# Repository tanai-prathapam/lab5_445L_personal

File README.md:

# Lab 5 Music Player and Audio Amp

# ECE445L-Lab5

Lab 5 Template.

## HW

The hw folder should contain your schematic and board files for your PCB or
circuits. In labs 3-11, you will be creating schematics for your circuit
in Kicad. 

## SW

The sw folder should contain your application firmware and software written for
the lab. The sw/inc folder contains firmware drivers written for you by
Professor Valvano. Feel free to write your own (in fact, in some labs, you may
be required to write your own).

You can place any other source files in the sw/ folder. TAs will look at the
files you create and/or modify for software quality and for running your
project.

## Resources

A couple files are provided in the Resources folder so you don't have to keep
searching for that one TI document. Some of them are immediately useful, like
the TM4C datasheet. Others may be useful for your final project, like the
TM4C_System_Design_Guidelines page.

## Git and Github

We will extensively use Git and Github for managing lab projects. This makes it
easier for TAs to grade and help debug the project by allowing the students to
see commit histories, maintain a common project structure, collaborate with
partners, merge different codebases, and to debug work.

Two common ways of using Git and Github are [Github Desktop](https://desktop.github.com/) and the [command line](https://git-scm.com/downloads). [Tutorials](https://dev.to/mollynem/git-github--workflow-fundamentals-5496) are also abundant on the net for you to peruse. We've provided a cheatsheet for git in the Resources folder.

It is highly recommended to make the most out of Git, even if you've never used
it before. Version control will save you a lot of suffering, and tools like Git
or SVN are ubiquitous in the industry.

## Lab Report

Following the lab doc provided at the root of this project, the TAs request you
submit a lab report in Microsoft Word (or Pages, if you're a Mac user). Please
name it `EID_lab_LAB_NUMBER_report.pdf`.

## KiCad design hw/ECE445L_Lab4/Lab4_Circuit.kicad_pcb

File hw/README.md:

# What to use?

For 319K/445L Lab 6 or 7, use the marked file. Otherwise use ECE445L_Starter.

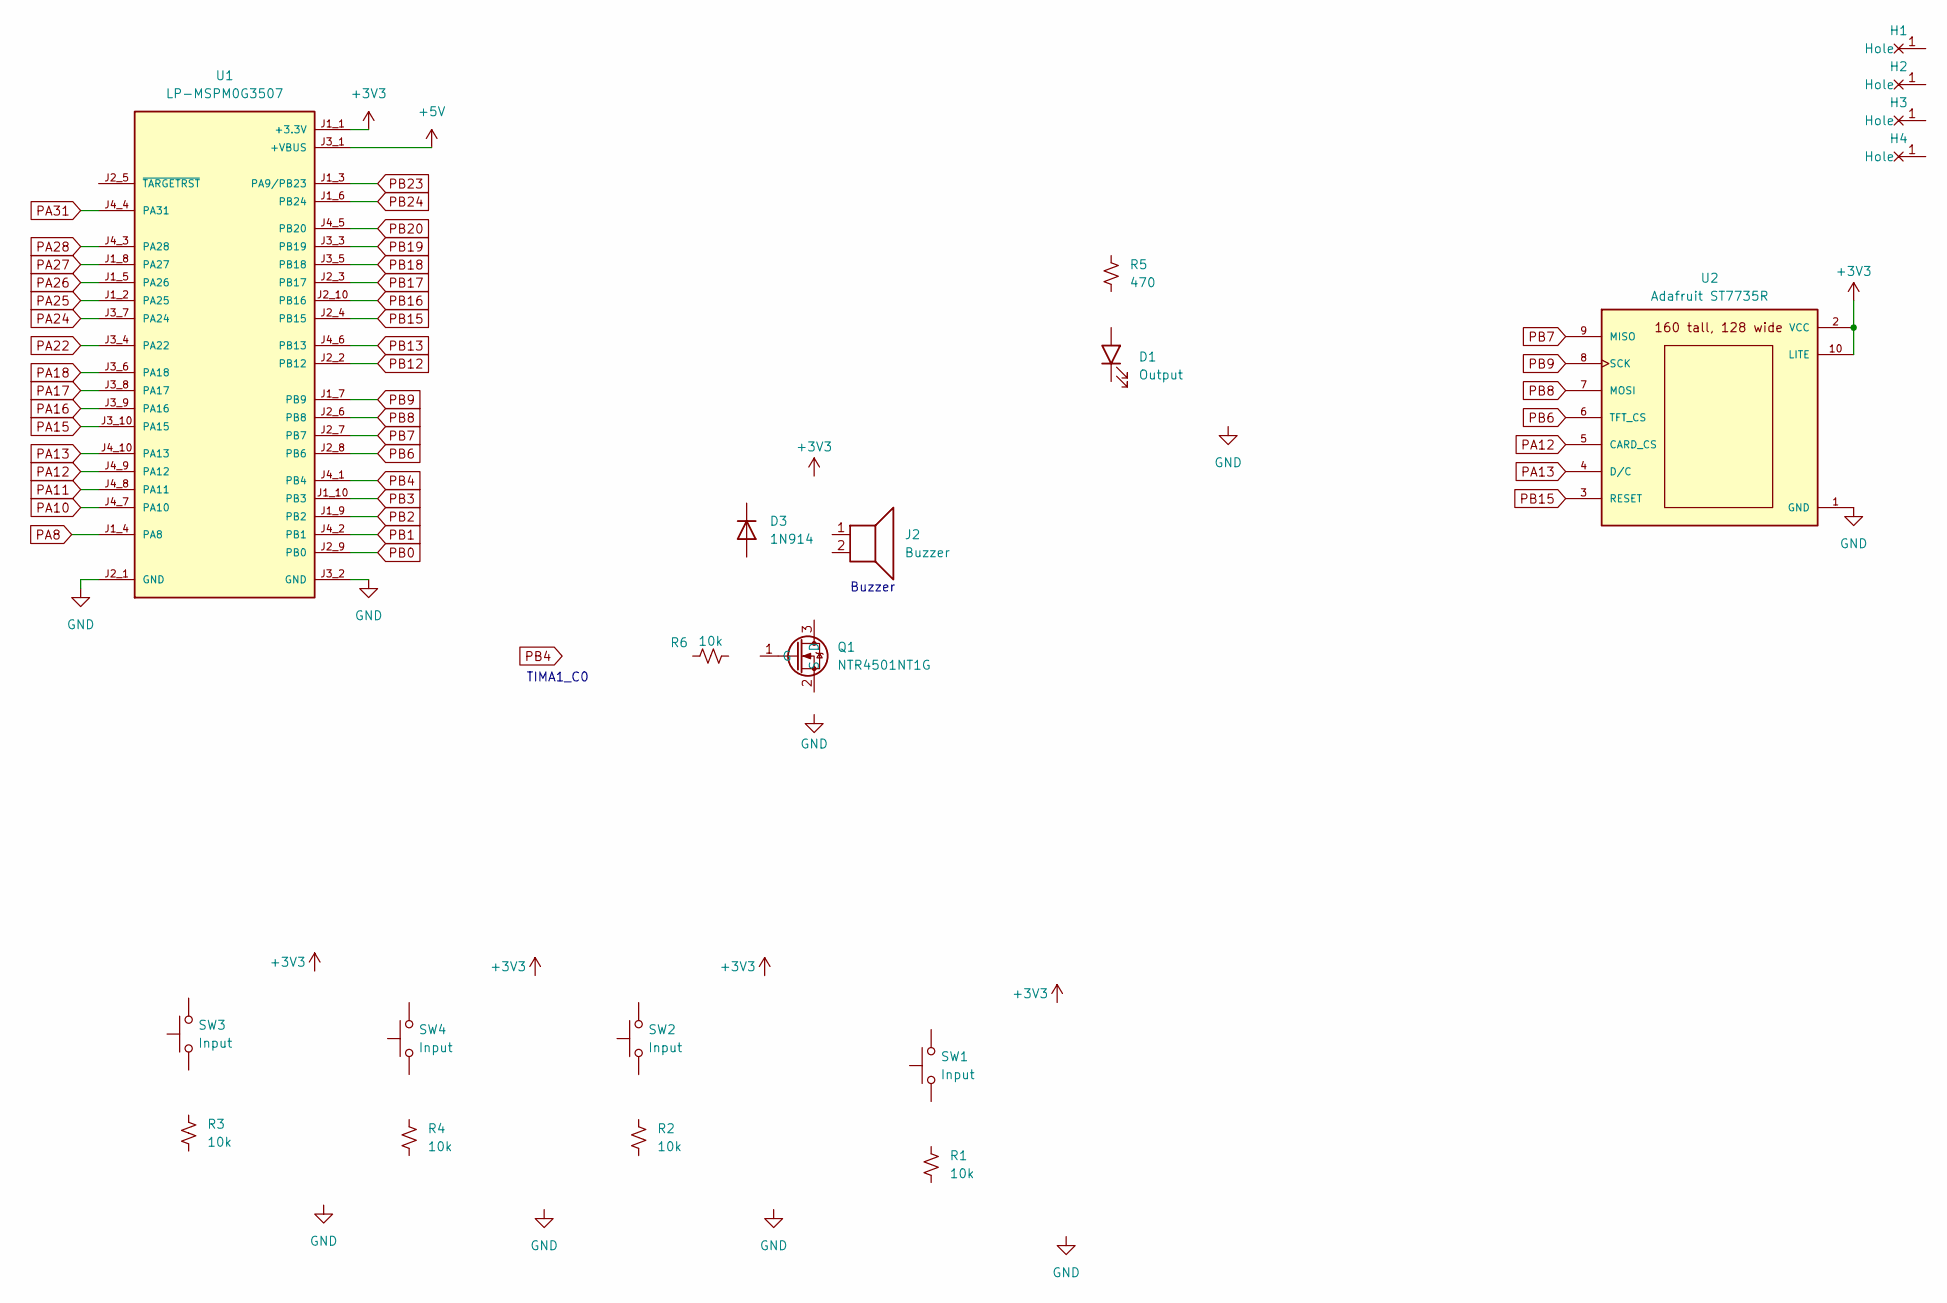
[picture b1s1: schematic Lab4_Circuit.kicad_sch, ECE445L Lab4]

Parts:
D1: Output; LED_D5.0mm
D3: 1N914; D_DO-35_SOD27_P7.62mm_Horizontal
H1, H2, H3, H4: MountingHole_4_40
J2: Buzzer; PinHeader_1x02_P2.54mm_Vertical
Q1: NTR4501NT1G; SOT96P237X111-3N; Mouser Part Number 863-NTR4501NT1G
R1, R2, R3, R4, R6: 10k; R_Axial_DIN0204_L3.6mm_D1.6mm_P7.62mm_Horizontal
R5: 470; R_Axial_DIN0204_L3.6mm_D1.6mm_P7.62mm_Horizontal
SW1, SW2, SW3, SW4: Input; SW_PUSH_6mm
U1: LP-MSPM0G3507; ti_LP_MSPM0G3507
U2: Adafruit ST7735R; adafruit_st7735r2

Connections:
+3V3: U1.J1_1 (+3.3V), U2.2 (VCC), U2.10 (LITE)
+5V: U1.J3_1 (+VBUS)
GND: U1.J2_1 (GND), U1.J3_2 (GND), U2.1 (GND)
PA8: U1.J1_4 (PA8)
PA10: U1.J4_7 (PA10)
PA11: U1.J4_8 (PA11)
PA12: U1.J4_9 (PA12), U2.5 (CARD_CS)
PA13: U1.J4_10 (PA13), U2.4 (D/C)
PA15: U1.J3_10 (PA15)
PA16: U1.J3_9 (PA16)
PA17: U1.J3_8 (PA17)
PA18: U1.J3_6 (PA18)
PA22: U1.J3_4 (PA22)
PA24: U1.J3_7 (PA24)
PA25: U1.J1_2 (PA25)
PA26: U1.J1_5 (PA26)
PA27: U1.J1_8 (PA27)
PA28: U1.J4_3 (PA28)
PA31: U1.J4_4 (PA31)
PB0: U1.J2_9 (PB0)
PB1: U1.J4_2 (PB1)
PB2: U1.J1_9 (PB2)
PB3: U1.J1_10 (PB3)
PB4: U1.J4_1 (PB4)
PB6: U1.J2_8 (PB6), U2.6 (TFT_CS)
PB7: U1.J2_7 (PB7), U2.9 (MISO)
PB8: U1.J2_6 (PB8), U2.7 (MOSI)
PB9: U1.J1_7 (PB9), U2.8 (SCK)
PB12: U1.J2_2 (PB12)
PB13: U1.J4_6 (PB13)
PB15: U1.J2_4 (PB15), U2.3 (RESET)
PB16: U1.J2_10 (PB16)
PB17: U1.J2_3 (PB17)
PB18: U1.J3_5 (PB18)
PB19: U1.J3_3 (PB19)
PB20: U1.J4_5 (PB20)
PB23: U1.J1_3 (PA9/PB23)
PB24: U1.J1_6 (PB24)

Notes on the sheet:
Buzzer
TIMA1_C0

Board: 2 copper layers, 20 parts (1 on the bottom side), 9 nets, no tracks yet.

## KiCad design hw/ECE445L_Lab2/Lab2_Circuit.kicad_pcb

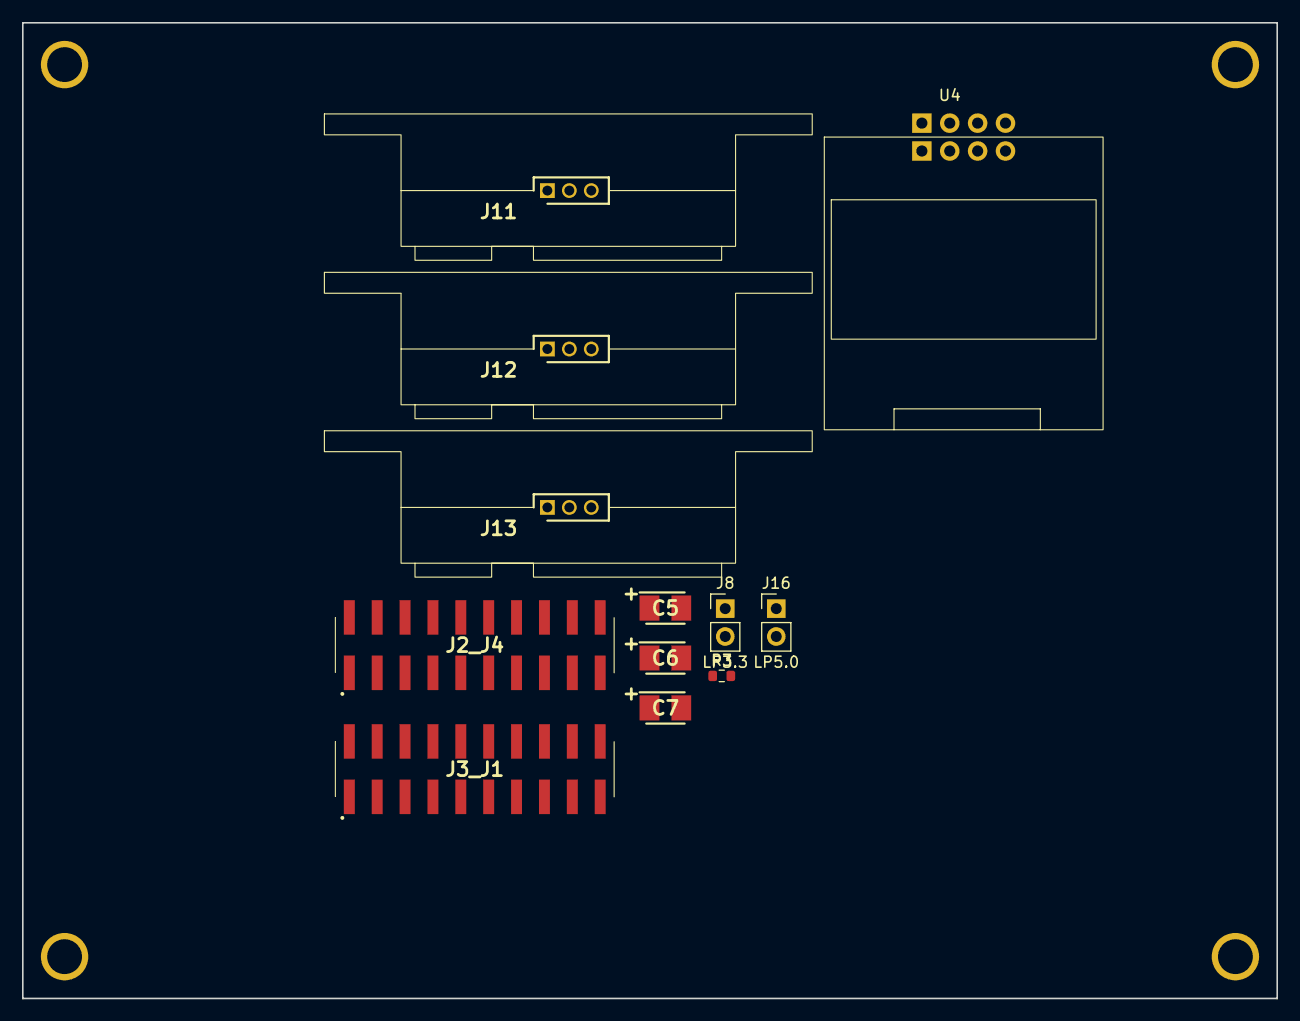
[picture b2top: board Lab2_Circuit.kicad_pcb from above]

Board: 2 copper layers, 114.3 x 88.9 mm, 16 parts (0 on the bottom side), 10 nets, no tracks yet.

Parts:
C5, C6, C7: 10uF; CAPPM3528X210N
H1, H2, H3, H4: MountingHole_4_40
J2_J4, J3_J1: LaunchPad
J8: LP3.3; PinHeader_1x02_P2.54mm_Vertical
J11, J12, J13: GP2Y0A41SK0F; SHDR3W50P0X200_1X3_650X240X440P
J16: LP5.0; PinHeader_1x02_P2.54mm_Vertical
R3: 1.5k; R_0603_1608Metric
U4: SSD1306

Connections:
+3V3: J8.1 (A), R3.1, U4.2 (VCC), U4.5 (VCC)
+5V: C5.1 (+), C6.1 (+), C7.1 (+), J11.3, J12.3, J13.3, J16.2 (B)
/LP3_3: J3_J1.1, J8.2 (B)
/VBUS: J3_J1.2, J16.1 (A)
GND: C5.2 (-), C6.2 (-), C7.2 (-), J2_J4.2, J3_J1.4, J11.2, J12.2, J13.2, U4.1 (GND), U4.6 (GND)
PA24: J3_J1.14, J13.1
PA26: J3_J1.9, J11.1
PB2: J3_J1.17, R3.2, U4.3 (SCL), U4.7 (SCL)
PB3: J3_J1.19, U4.4 (SDA), U4.8 (SDA)
PB24: J3_J1.11, J12.1

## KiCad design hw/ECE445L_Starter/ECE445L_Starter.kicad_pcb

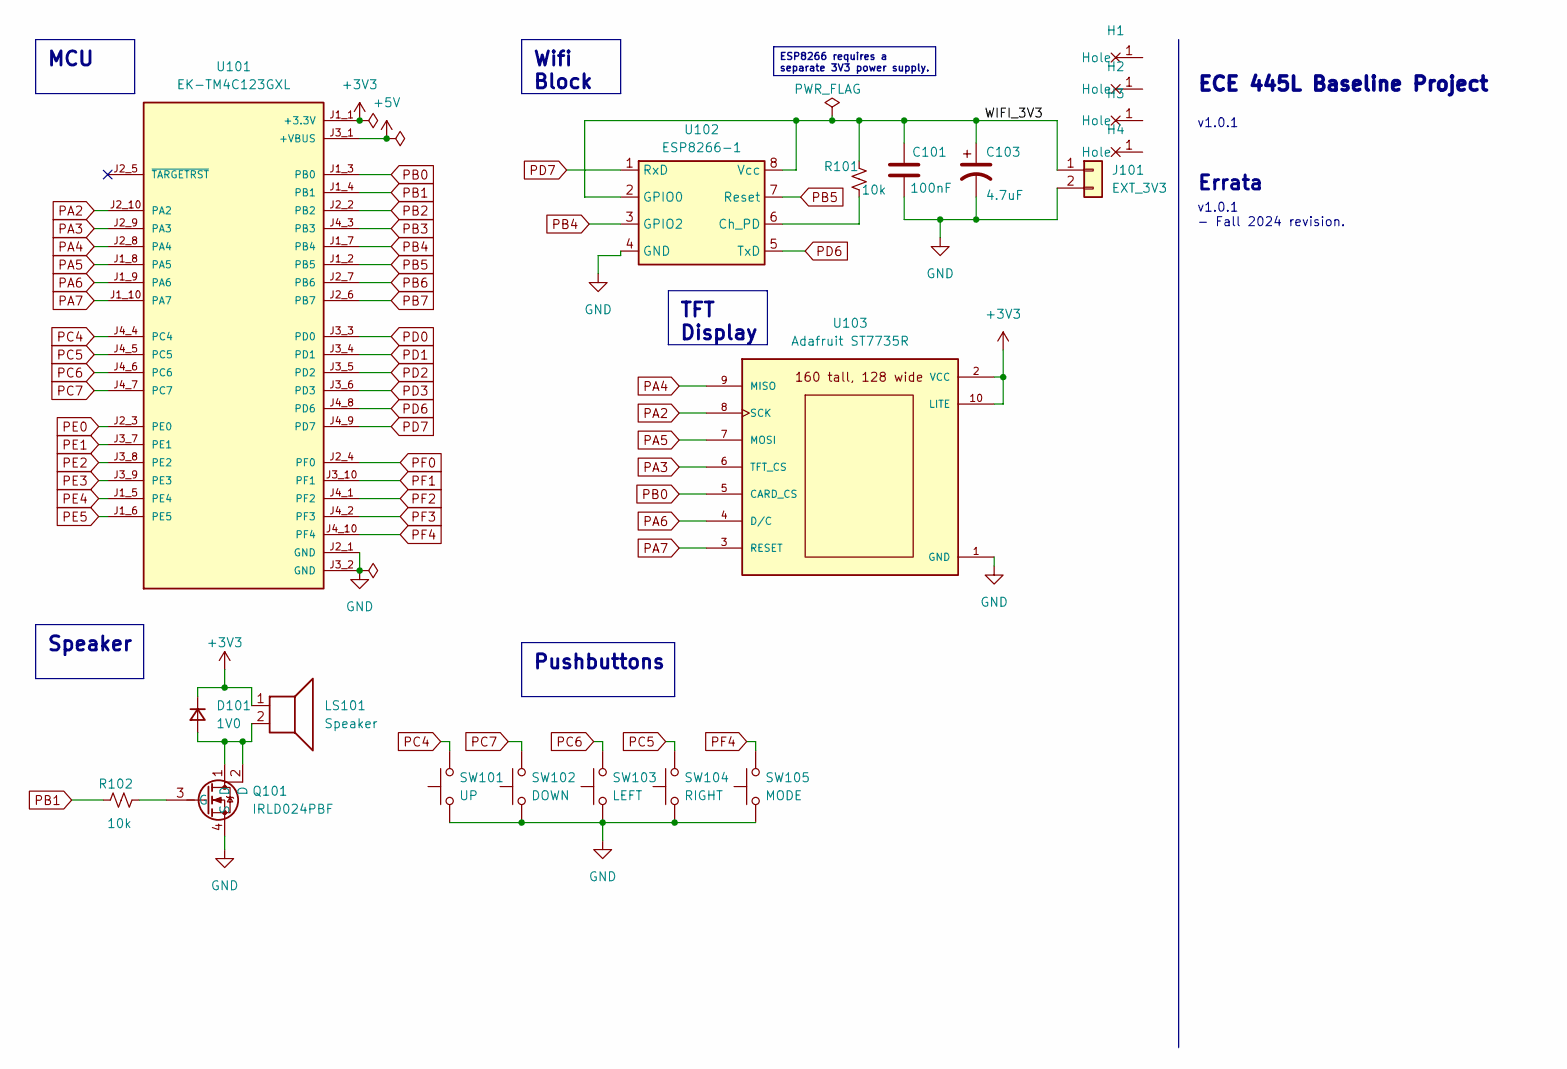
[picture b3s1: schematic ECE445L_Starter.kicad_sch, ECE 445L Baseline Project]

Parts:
C101: 100nF; C_Axial_200mil
C103: 4.7uF; CP_Radial_Tantal200mil
D101: 1V0; D_5W_P12.70mm_Horizontal
H1, H2, H3, H4: MountingHole_4_40
J101: EXT_3V3; Samtec_HPM-02-01-x-S_Straight_1x02_Pitch5.08mm
LS101: Speaker; PinHeader_1x02_P2.54mm_Vertical
Q101: IRLD024PBF; DIP920W60P254L490H457Q4N; Mouser Part Number 844-IRLD024PBF
R101, R102: 10k; R_Axial_DIN0204_L3.6mm_D1.6mm_P7.62mm_Horizontal
SW101: UP; SW_PUSH_6mm
SW102: DOWN; SW_PUSH_6mm
SW103: LEFT; SW_PUSH_6mm
SW104: RIGHT; SW_PUSH_6mm
SW105: MODE; SW_PUSH_6mm
U101: EK-TM4C123GXL; ti_EKTM4C123GXL
U102: ESP8266-1; ESP8266_FemaleConnector
U103: Adafruit ST7735R; adafruit_st7735r2

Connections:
+3V3: D101.1 (K), LS101.1, U101.J1_1 (+3.3V), U103.2 (VCC), U103.10 (LITE)
+5V: U101.J3_1 (+VBUS)
/WIFI_3V3: C101.1, C103.1, J101.1, R101.1, U102.2 (GPIO0), U102.8 (Vcc)
GND: C101.2, C103.2, J101.2, Q101.4 (S), SW101.1, SW102.1, SW103.1, SW104.1, SW105.1, U101.J2_1 (GND), U101.J3_2 (GND), U102.4 (GND), U103.1 (GND)
unnamed: D101.2 (A), LS101.2, Q101.1 (D), Q101.2 (D)
unnamed: Q101.3 (G), R102.2
unnamed: R101.2, U102.6 (Ch_PD)
PA2: U101.J2_10 (PA2), U103.8 (SCK)
PA3: U101.J2_9 (PA3), U103.6 (TFT_CS)
PA4: U101.J2_8 (PA4), U103.9 (MISO)
PA5: U101.J1_8 (PA5), U103.7 (MOSI)
PA6: U101.J1_9 (PA6), U103.4 (D/C)
PA7: U101.J1_10 (PA7), U103.3 (RESET)
PB0: U101.J1_3 (PB0), U103.5 (CARD_CS)
PB1: R102.1, U101.J1_4 (PB1)
PB2: U101.J2_2 (PB2)
PB3: U101.J4_3 (PB3)
PB4: U101.J1_7 (PB4), U102.3 (GPIO2)
PB5: U101.J1_2 (PB5), U102.7 (Reset)
PB6: U101.J2_7 (PB6)
PB7: U101.J2_6 (PB7)
PC4: SW101.2, U101.J4_4 (PC4)
PC5: SW104.2, U101.J4_5 (PC5)
PC6: SW103.2, U101.J4_6 (PC6)
PC7: SW102.2, U101.J4_7 (PC7)
PD0: U101.J3_3 (PD0)
PD1: U101.J3_4 (PD1)
PD2: U101.J3_5 (PD2)
PD3: U101.J3_6 (PD3)
PD6: U101.J4_8 (PD6), U102.5 (TxD)
PD7: U101.J4_9 (PD7), U102.1 (RxD)
PE0: U101.J2_3 (PE0)
PE1: U101.J3_7 (PE1)
PE2: U101.J3_8 (PE2)
PE3: U101.J3_9 (PE3)
PE4: U101.J1_5 (PE4)
PE5: U101.J1_6 (PE5)
PF0: U101.J2_4 (PF0)
PF1: U101.J3_10 (PF1)
PF2: U101.J4_1 (PF2)
PF3: U101.J4_2 (PF3)
PF4: SW105.2, U101.J4_10 (PF4)

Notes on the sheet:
v1.0.1 - Fall 2024 revision.
ECE 445L Baseline Project
v1.0.1
Errata
MCU
ESP8266 requires a separate 3V3 power supply.
Speaker
Pushbuttons
TFT Display
Wifi Block

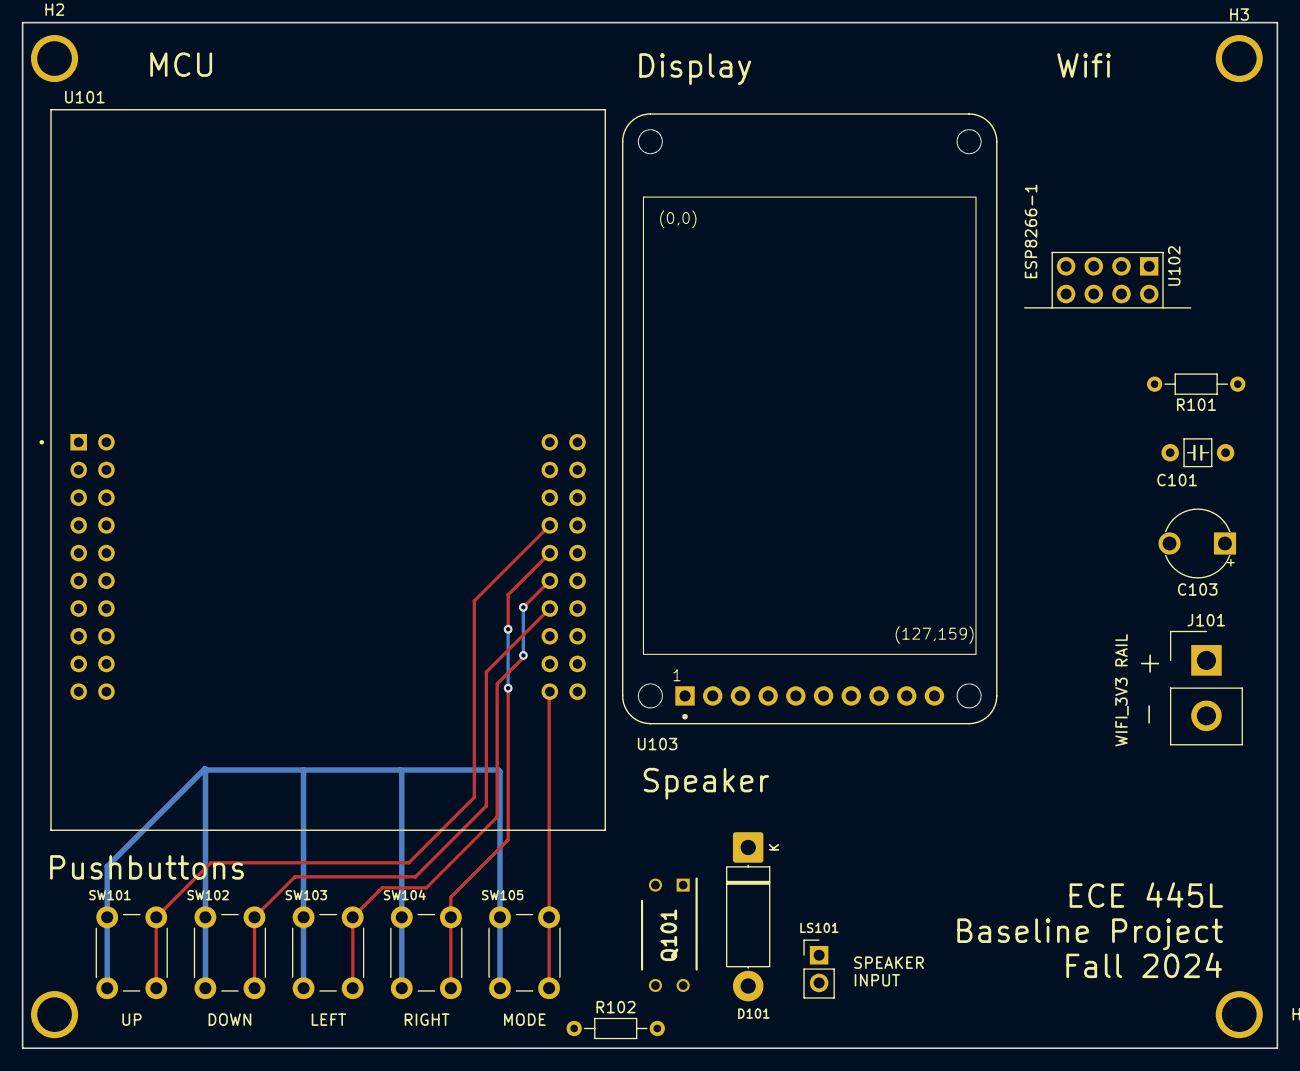
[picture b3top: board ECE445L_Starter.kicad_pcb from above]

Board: 2 copper layers, 115.0 x 94.0 mm, 20 parts (0 on the bottom side), 23 nets.

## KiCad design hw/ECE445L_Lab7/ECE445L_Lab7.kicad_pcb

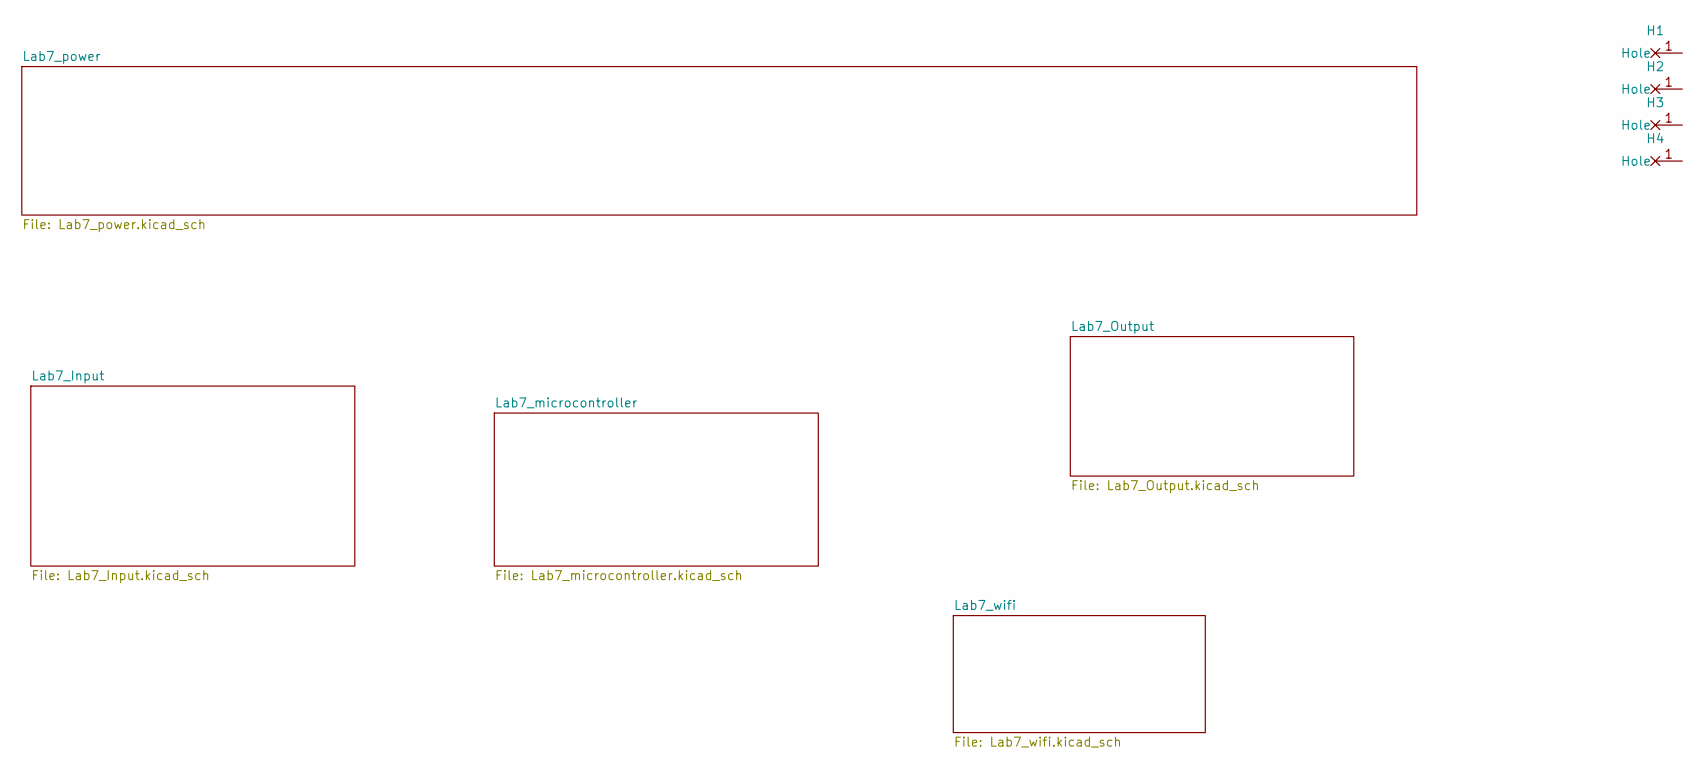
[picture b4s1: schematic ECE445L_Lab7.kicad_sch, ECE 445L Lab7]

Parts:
H1, H2, H3, H4: MountingHole_4_40

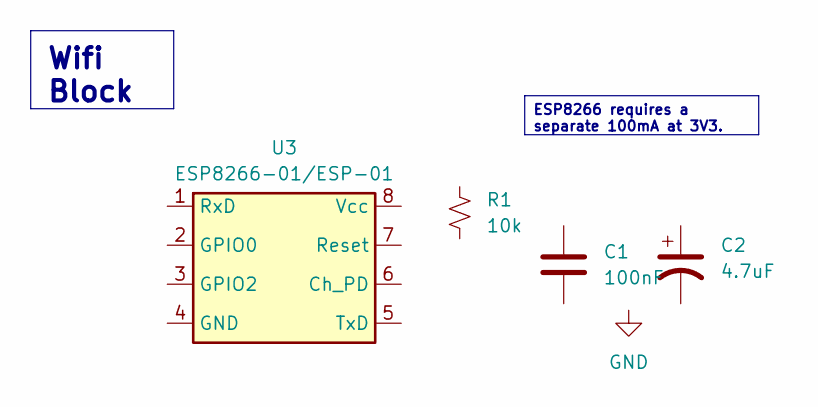
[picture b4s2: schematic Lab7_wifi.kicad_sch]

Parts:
C1: 100nF; C_Axial_200mil
C2: 4.7uF; CP_Radial_Tantal200mil
R1: 10k; R_Axial_DIN0204_L3.6mm_D1.6mm_P7.62mm_Horizontal
U3: ESP8266-01/ESP-01; ESP8266_FemaleConnector

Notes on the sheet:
ESP8266 requires a separate 100mA at 3V3.
Wifi Block

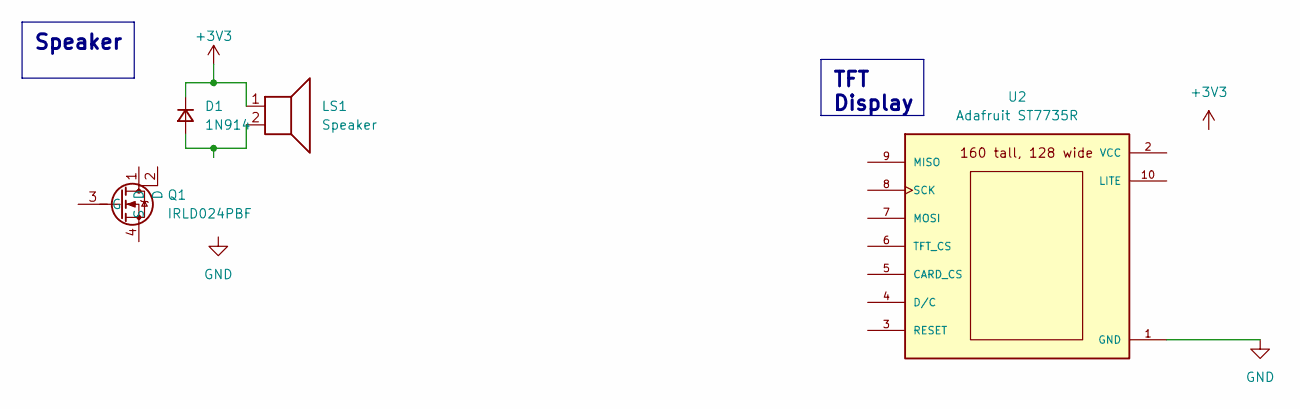
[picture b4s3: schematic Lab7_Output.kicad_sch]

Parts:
D1: 1N914; D_5W_P12.70mm_Horizontal
LS1: Speaker; PinHeader_1x02_P2.54mm_Vertical
Q1: IRLD024PBF; DIP920W60P254L490H457Q4N; Mouser Part Number 844-IRLD024PBF
U2: Adafruit ST7735R; adafruit_st7735r2

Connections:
+3V3: D1.1 (K), LS1.1; also elsewhere on the board
GND: U2.1 (GND); also elsewhere on the board
unnamed: D1.2 (A), LS1.2

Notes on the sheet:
TFT Display
Speaker

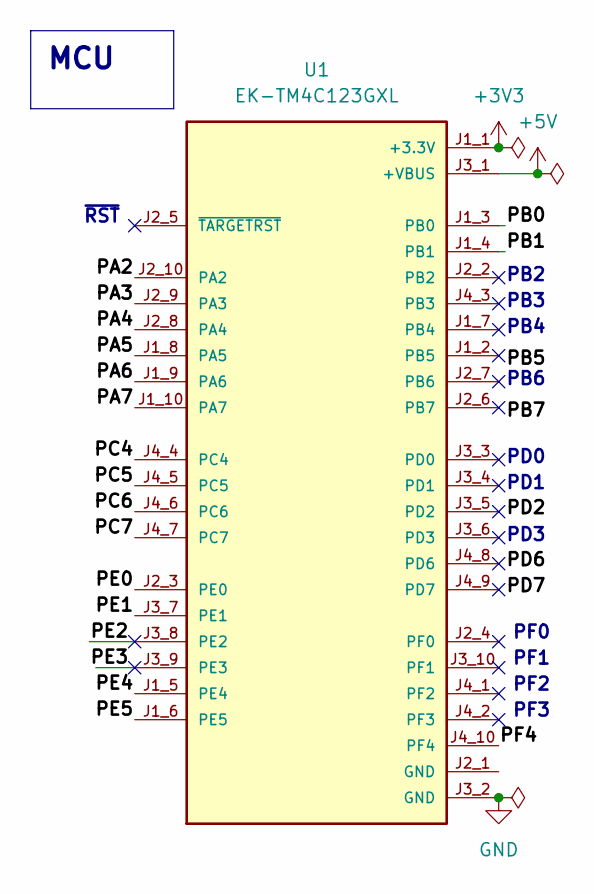
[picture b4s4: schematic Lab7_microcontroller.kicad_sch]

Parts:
U1: EK-TM4C123GXL; ti_EKTM4C123GXL

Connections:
+3V3: U1.J1_1 (+3.3V); also elsewhere on the board
+5V: U1.J3_1 (+VBUS)
/Lab7_microcontroller/PA2: U1.J2_10 (PA2)
/Lab7_microcontroller/PA3: U1.J2_9 (PA3)
/Lab7_microcontroller/PA4: U1.J2_8 (PA4)
/Lab7_microcontroller/PA5: U1.J1_8 (PA5)
/Lab7_microcontroller/PA6: U1.J1_9 (PA6)
/Lab7_microcontroller/PA7: U1.J1_10 (PA7)
/Lab7_microcontroller/PB0: U1.J1_3 (PB0)
/Lab7_microcontroller/PB1: U1.J1_4 (PB1)
/Lab7_microcontroller/PC4: U1.J4_4 (PC4)
/Lab7_microcontroller/PC5: U1.J4_5 (PC5)
/Lab7_microcontroller/PC6: U1.J4_6 (PC6)
/Lab7_microcontroller/PC7: U1.J4_7 (PC7)
/Lab7_microcontroller/PE0: U1.J2_3 (PE0)
/Lab7_microcontroller/PE1: U1.J3_7 (PE1)
/Lab7_microcontroller/PE2: U1.J3_8 (PE2)
/Lab7_microcontroller/PE4: U1.J1_5 (PE4)
/Lab7_microcontroller/PE5: U1.J1_6 (PE5)
/Lab7_microcontroller/PF4: U1.J4_10 (PF4)
GND: U1.J3_2 (GND); also elsewhere on the board

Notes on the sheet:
~{RST}
PB2
PD3
PF3
PB3
PB4
PD1
PF1
PB6
PD0
PF2
PF0
MCU

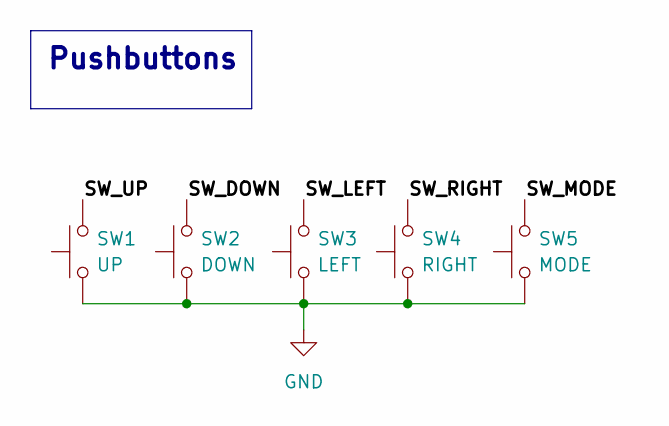
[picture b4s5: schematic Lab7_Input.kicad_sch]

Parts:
SW1: UP; SW_PUSH_6mm
SW2: DOWN; SW_PUSH_6mm
SW3: LEFT; SW_PUSH_6mm
SW4: RIGHT; SW_PUSH_6mm
SW5: MODE; SW_PUSH_6mm

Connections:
/Lab7_Input/SW_DOWN: SW2.2
/Lab7_Input/SW_LEFT: SW3.2
/Lab7_Input/SW_MODE: SW5.2
/Lab7_Input/SW_RIGHT: SW4.2
/Lab7_Input/SW_UP: SW1.2
GND: SW1.1, SW2.1, SW3.1, SW4.1, SW5.1; also elsewhere on the board

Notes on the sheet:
Pushbuttons

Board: 2 copper layers, 18 parts (0 on the bottom side), 3 nets, no tracks yet.

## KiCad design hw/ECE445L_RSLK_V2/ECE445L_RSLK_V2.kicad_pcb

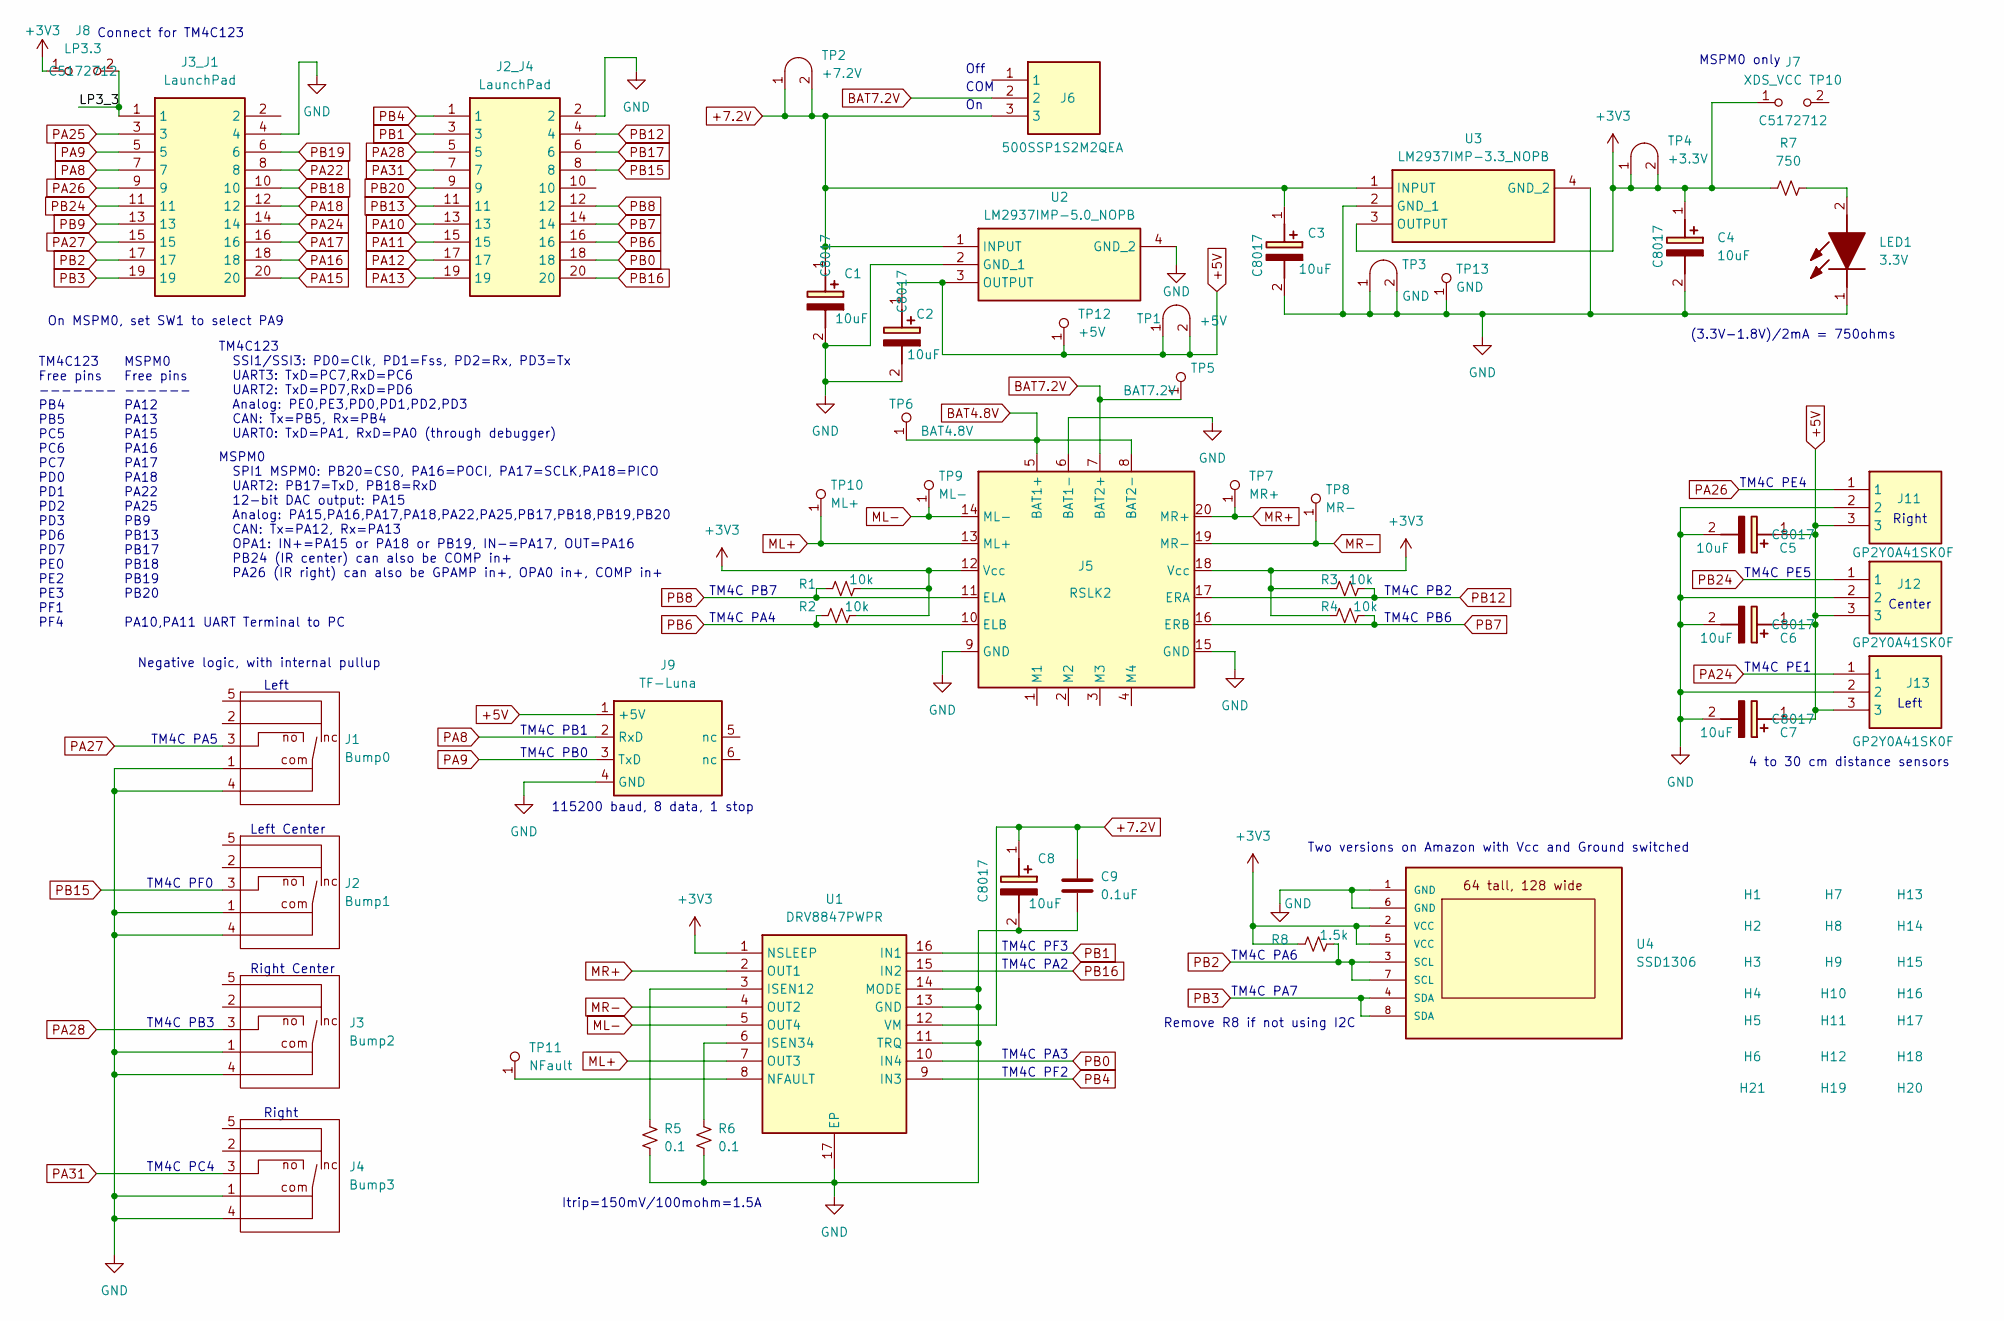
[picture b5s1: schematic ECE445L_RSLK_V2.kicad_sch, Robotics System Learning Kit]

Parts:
C1, C2, C3, C4, C5, C6, C7, C8: 10uF; CAPPM3528X210N; Mouser Part Number 581-TAJB106K020R
C9: 0.1uF; C_0603_1608Metric; LCSC C5186689
H1, H2, H3, H4, H5, H6, H7, H8, H9, H10, H11, H12, H13, H14, H15, H16, H17, H18, H19, H20, H21: MountingHole_4_40
J1: Bump0; D2F-01L30-D3_5pin
J2: Bump1; D2F-01L30-D3_5pin
J2_J4, J3_J1: LaunchPad; Mouser Part Number 855-M20-8761042P
J3: Bump2; D2F-01L30-D3_5pin
J4: Bump3; D2F-01L30-D3_5pin
J5: RSLK2; RSLK_Chassis
J6: 500SSP1S2M2QEA; Mouser Part Number 612-500SSP1S2M2QEA
J7: XDS_VCC TP10; PinHeader_1x02_P2.54mm_Vertical; LCSC C5172712
J8: LP3.3; PinHeader_1x02_P2.54mm_Vertical; LCSC C5172712
J9: TF-Luna; JST-GH_1x06_1.25mm
J11, J12, J13: GP2Y0A41SK0F; SHDR3W50P0X200_1X3_650X240X440P; Mouser Part Number 855-M22-7130342
LED1: 3.3V; APT1608CGCK; Mouser Part Number 604-APTD1608LSECKJ3F
R1, R2, R3, R4: 10k; R_0603_1608Metric; LCSC C340542
R5, R6: 0.1; R_1206_3216Metric; LCSC C2889036
R7: 750; R_0603_1608Metric; LCSC C365210
R8: 1.5k; R_0603_1608Metric; LCSC C216914
TP1: +5V; Testpoint_1x02_P2.54mm
TP2: +7.2V; Testpoint_1x02_P2.54mm
TP3: GND; Testpoint_1x02_P2.54mm
TP4: +3.3V; Testpoint_1x02_P2.54mm
TP5: BAT7.2V; Testpoint_1x1
TP6: BAT4.8V; Testpoint_1x1
TP7: MR+; Testpoint_1x1
TP8: MR-; Testpoint_1x1
TP9: ML-; Testpoint_1x1
TP10: ML+; Testpoint_1x1
TP11: NFault; Testpoint_1x1
TP12: +5V; Testpoint_1x1
TP13: GND; Testpoint_1x1
U1: DRV8847PWPR; SOP65P640X120-17N; Mouser Part Number 595-DRV8847PWPR
U2: LM2937IMP-5.0_NOPB; SOT230P700X180-4N; Mouser Part Number 926-LM2937IMP5.0NOPB
U3: LM2937IMP-3.3_NOPB; SOT230P700X180-4N; Mouser Part Number 926-LM2937IMP3.3NOPB
U4: SSD1306

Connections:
+3V3: C4.1 (+), J5.12 (Vcc), J5.18 (Vcc), J7.1 (A), J8.1 (A), R1.2, R2.2, R3.1, R4.1, R7.2, R8.1, TP4.1 (A), TP4.2 (B), U1.1 (NSLEEP), U3.3 (OUTPUT), U4.2 (VCC), U4.5 (VCC)
+5V: C2.1 (+), C5.1 (+), C6.1 (+), C7.1 (+), J9.1 (+5V), J11.3, J12.3, J13.3, TP1.1 (A), TP1.2 (B), TP12.1 (A), U2.3 (OUTPUT)
+7.2V: C1.1 (+), C3.1 (+), C8.1 (+), C9.1, J6.3, TP2.1 (A), TP2.2 (B), U1.12 (VM), U2.1 (INPUT), U3.1 (INPUT)
/LP3_3: J3_J1.1, J8.2 (B)
BAT4.8V: J5.5 (BAT1+), J5.8 (BAT2-), TP6.1 (A)
BAT7.2V: J5.7 (BAT2+), J6.2, TP5.1 (A)
GND: C1.2 (-), C2.2 (-), C3.2 (-), C4.2 (-), C5.2 (-), C6.2 (-), C7.2 (-), C8.2 (-), C9.2, J1.1 (com), J1.4 (com), J2.1 (com), J2.4 (com), J2_J4.2, J3.1 (com), J3.4 (com), J3_J1.4, J4.1 (com), J4.4 (com), J5.6 (BAT1-), J5.9 (GND), J5.15 (GND), J9.4 (GND), J11.2, J12.2, J13.2, LED1.1 (K), R5.2, R6.2, TP3.1 (A), TP3.2 (B), TP13.1 (A), U1.11 (TRQ), U1.13 (GND), U1.14 (MODE), U1.17 (EP), U2.2 (GND_1), U2.4 (GND_2), U3.2 (GND_1), U3.4 (GND_2), U4.1 (GND), U4.6 (GND)
ML+: J5.13 (ML+), TP10.1 (A), U1.7 (OUT3)
ML-: J5.14 (ML-), TP9.1 (A), U1.5 (OUT4)
MR+: J5.20 (MR+), TP7.1 (A), U1.2 (OUT1)
MR-: J5.19 (MR-), TP8.1 (A), U1.4 (OUT2)
unnamed: LED1.2 (A), R7.1
unnamed: TP11.1 (A), U1.8 (NFAULT)
unnamed: R5.1, U1.3 (ISEN12)
unnamed: R6.1, U1.6 (ISEN34)
PA8: J3_J1.7, J9.2 (RxD)
PA9: J3_J1.5, J9.3 (TxD)
PA10: J2_J4.13
PA11: J2_J4.15
PA12: J2_J4.17
PA13: J2_J4.19
PA15: J3_J1.20
PA16: J3_J1.18
PA17: J3_J1.16
PA18: J3_J1.12
PA22: J3_J1.8
PA24: J3_J1.14, J13.1
PA25: J3_J1.3
PA26: J3_J1.9, J11.1
PA27: J1.3 (no), J3_J1.15
PA28: J2_J4.5, J3.3 (no)
PA31: J2_J4.7, J4.3 (no)
PB0: J2_J4.18, U1.10 (IN4)
PB1: J2_J4.3, U1.16 (IN1)
PB2: J3_J1.17, R8.2, U4.3 (SCL), U4.7 (SCL)
PB3: J3_J1.19, U4.4 (SDA), U4.8 (SDA)
PB4: J2_J4.1, U1.9 (IN3)
PB6: J2_J4.16, J5.10 (ELB), R2.1
PB7: J2_J4.14, J5.16 (ERB), R4.2
PB8: J2_J4.12, J5.11 (ELA), R1.1
PB9: J3_J1.13
PB12: J2_J4.4, J5.17 (ERA), R3.2
PB13: J2_J4.11
PB15: J2.3 (no), J2_J4.8
PB16: J2_J4.20, U1.15 (IN2)
PB17: J2_J4.6
PB18: J3_J1.10
PB19: J3_J1.6
PB20: J2_J4.9
PB24: J3_J1.11, J12.1

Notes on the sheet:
TM4C PB7
TM4C PE5
Negative logic, with internal pullup
TM4C PF2
TM4C PC4
115200 baud, 8 data, 1 stop
Right
TM4C PA3
MSPM0 Free pins ------ PA12 PA13 PA15 PA16 PA17 PA18 PA22 PA25 PB9 PB13 PB17 PB18 PB19 PB20 PA10,PA11 UART Terminal to PC
TM4C PB2
TM4C123 Free pins ------- PB4 PB5 PC5 PC6 PC7 PD0 PD1 PD2 PD3 PD6 PD7 PE0 PE2 PE3 PF1 PF4
TM4C PA4
Left Center
Connect for TM4C123
Left
TM4C PF3
TM4C PA6
MSPM0 SPI1 MSPM0: PB20=CS0, PA16=POCI, PA17=SCLK,PA18=PICO UART2: PB17=TxD, PB18=RxD 12-bit DAC output: PA15 Analog: PA15,PA16,PA17,PA18,PA22,PA25,PB17,PB18,PB19,PB20 CAN: Tx=PA12, Rx=PA13 OPA1: IN+=PA15 or PA18 or PB19, IN-=PA17, OUT=PA16 PB24 (IR center) can also be COMP in+ PA26 (IR right) can a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
TM4C PB1
TM4C PF0
Two versions on Amazon with Vcc and Ground switched
Itrip=150mV/100mohm=1.5A
TM4C PA5
Off
4 to 30 cm distance sensors
TM4C PB6
On MSPM0, set SW1 to select PA9
Remove R8 if not using I2C
TM4C PB0
Right Center
Center
TM4C PE4
(3.3V-1.8V)/2mA = 750ohms
TM4C PB3
TM4C PA7
MSPM0 only
COM
TM4C PE1
TM4C PA2
TM4C123 SSI1/SSI3: PD0=Clk, PD1=Fss, PD2=Rx, PD3=Tx UART3: TxD=PC7,RxD=PC6 UART2: TxD=PD7,RxD=PD6 Analog: PE0,PE3,PD0,PD1,PD2,PD3 CAN: Tx=PB5, Rx=PB4 UART0: TxD=PA1, RxD=PA0 (through debugger)
